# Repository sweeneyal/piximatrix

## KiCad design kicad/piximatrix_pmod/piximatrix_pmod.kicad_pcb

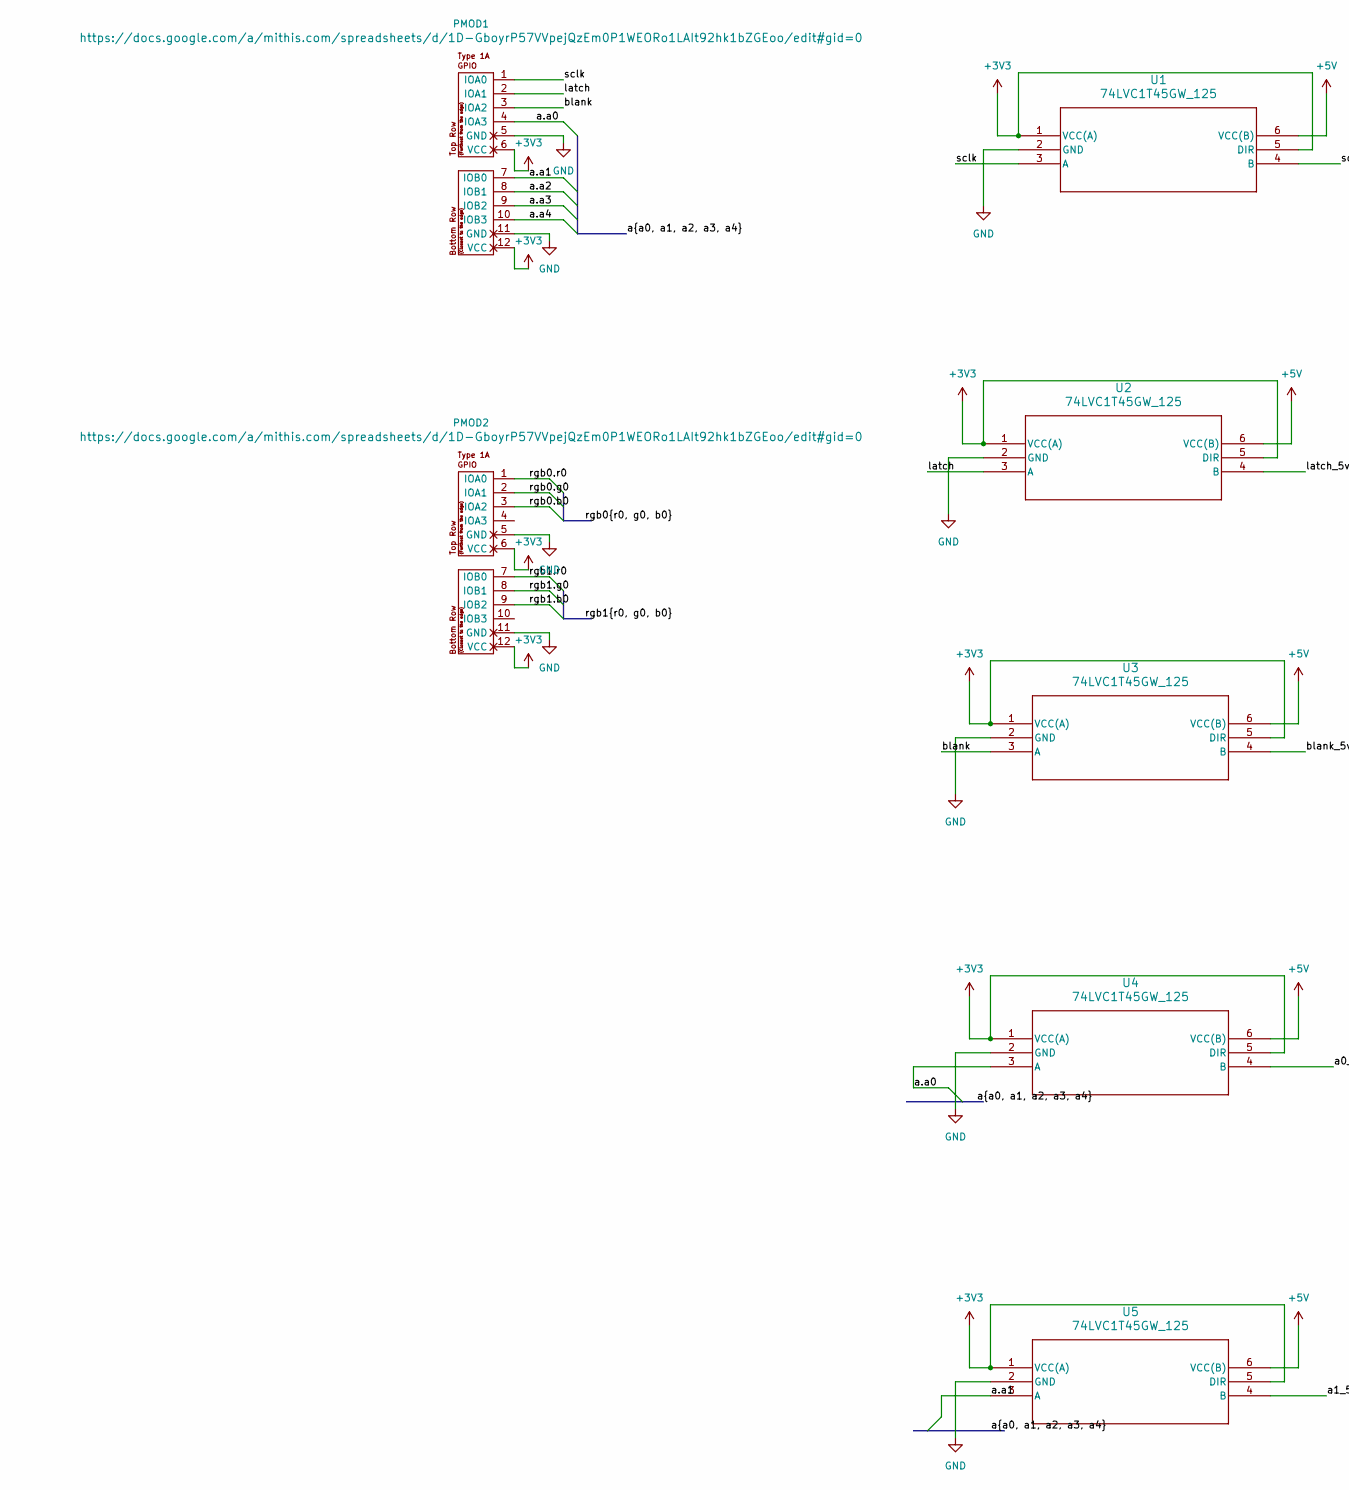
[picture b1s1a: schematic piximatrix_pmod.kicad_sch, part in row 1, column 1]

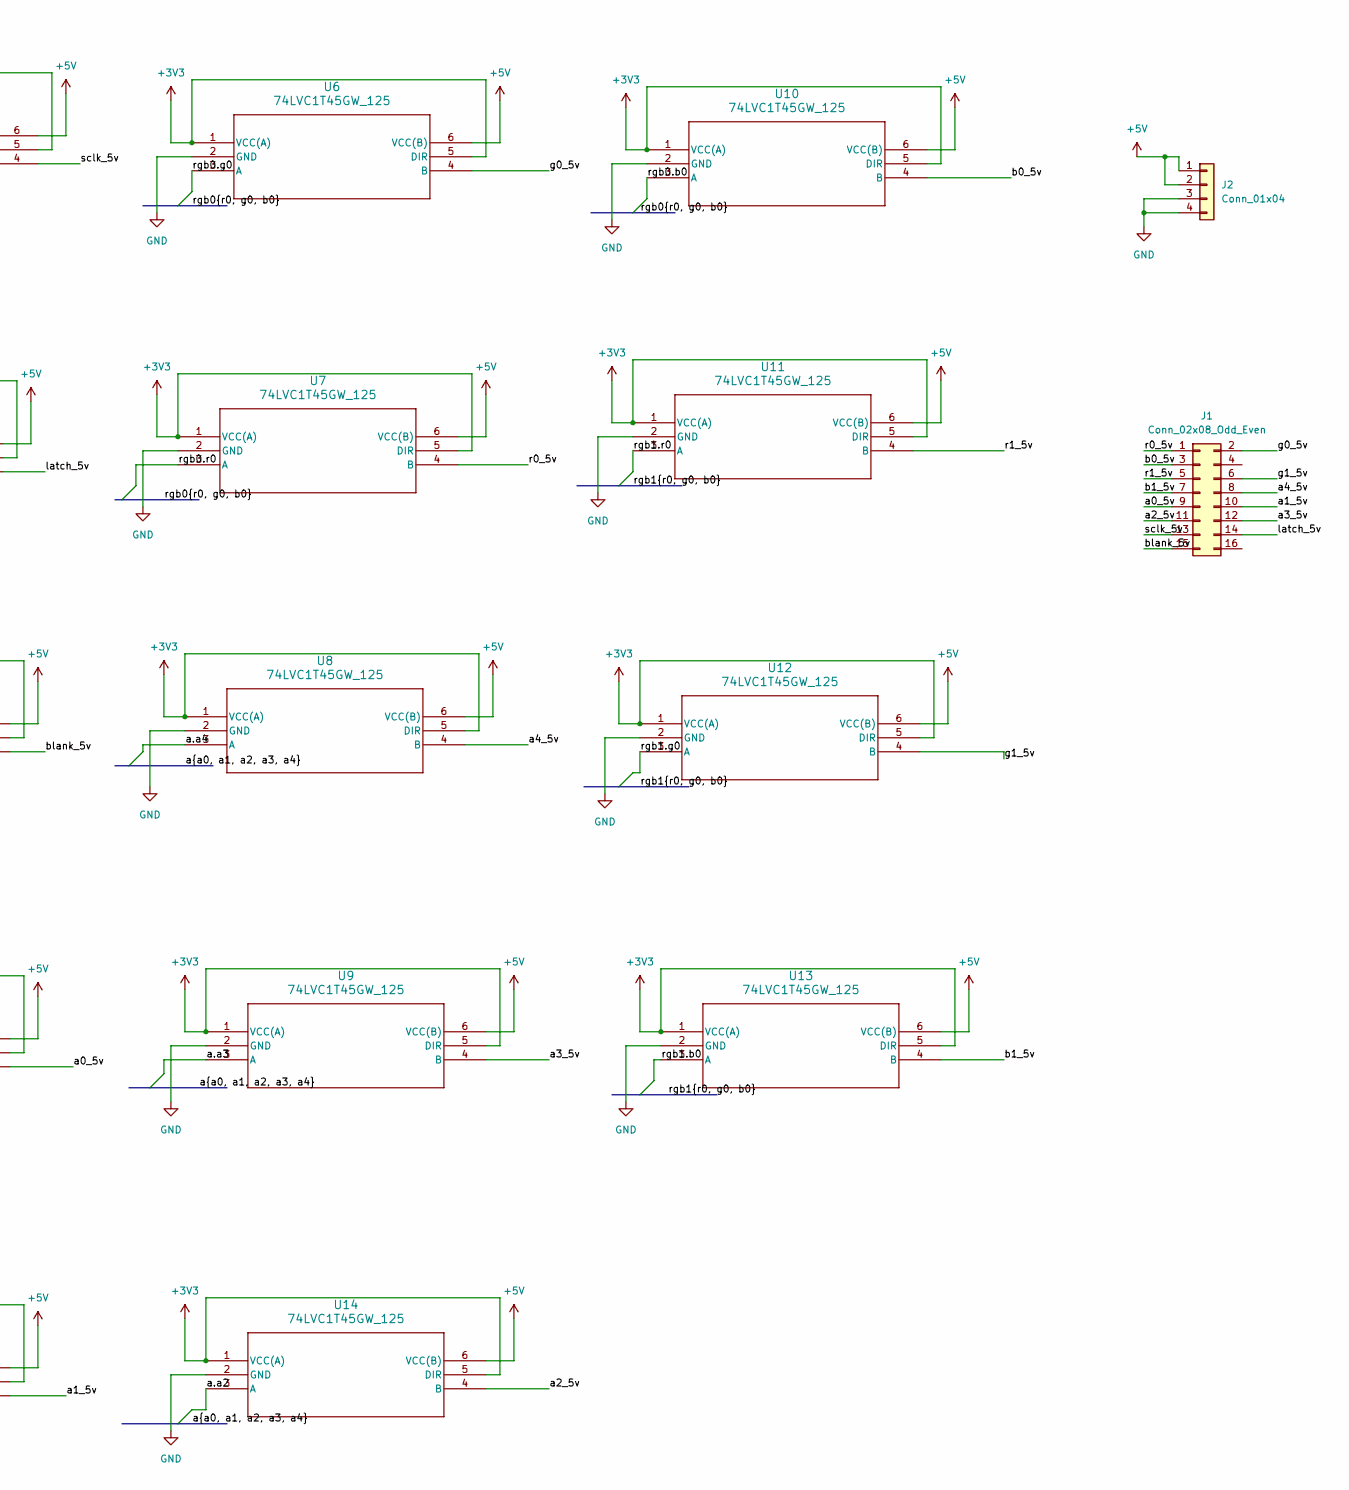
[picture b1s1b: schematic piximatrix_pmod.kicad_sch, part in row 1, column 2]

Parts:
J1: Conn_02x08_Odd_Even; IDC-Header_2x08_P2.54mm_Vertical
J2: Conn_01x04; Molex_KK-396_A-41791-0004_1x04_P3.96mm_Vertical
PMOD1, PMOD2: PMOD-Device-x2-Type-1A-GPIO; pmod_pin_array_6x2
U1, U2, U3, U4, U5, U6, U7, U8, U9, U10, U11, U12, U13, U14: 74LVC1T45GW_125; TSSOP6_SOT363-2_NEX

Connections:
+3V3: PMOD1.6 (VCC), PMOD1.12 (VCC), PMOD2.6 (VCC), PMOD2.12 (VCC), U1.1 (VCC(A)), U1.5 (DIR), U2.1 (VCC(A)), U2.5 (DIR), U3.1 (VCC(A)), U3.5 (DIR), U4.1 (VCC(A)), U4.5 (DIR), U5.1 (VCC(A)), U5.5 (DIR), U6.1 (VCC(A)), U6.5 (DIR), U7.1 (VCC(A)), U7.5 (DIR), U8.1 (VCC(A)), U8.5 (DIR), U9.1 (VCC(A)), U9.5 (DIR), U10.1 (VCC(A)), U10.5 (DIR), U11.1 (VCC(A)), U11.5 (DIR), U12.1 (VCC(A)), U12.5 (DIR), U13.1 (VCC(A)), U13.5 (DIR), U14.1 (VCC(A)), U14.5 (DIR)
+5V: J2.1, J2.2, U1.6 (VCC(B)), U2.6 (VCC(B)), U3.6 (VCC(B)), U4.6 (VCC(B)), U5.6 (VCC(B)), U6.6 (VCC(B)), U7.6 (VCC(B)), U8.6 (VCC(B)), U9.6 (VCC(B)), U10.6 (VCC(B)), U11.6 (VCC(B)), U12.6 (VCC(B)), U13.6 (VCC(B)), U14.6 (VCC(B))
/a0_5v: J1.9, U4.4 (B)
/a1_5v: J1.10, U5.4 (B)
/a2_5v: J1.11, U14.4 (B)
/a3_5v: J1.12, U9.4 (B)
/a4_5v: J1.8, U8.4 (B)
/a.a0: PMOD1.4 (IOA3), U4.3 (A)
/a.a1: PMOD1.7 (IOB0), U5.3 (A)
/a.a2: PMOD1.8 (IOB1), U14.3 (A)
/a.a3: PMOD1.9 (IOB2), U9.3 (A)
/a.a4: PMOD1.10 (IOB3), U8.3 (A)
/b0_5v: J1.3, U10.4 (B)
/b1_5v: J1.7, U13.4 (B)
/blank: PMOD1.3 (IOA2), U3.3 (A)
/blank_5v: J1.15, U3.4 (B)
/g0_5v: J1.2, U6.4 (B)
/g1_5v: J1.6, U12.4 (B)
/latch: PMOD1.2 (IOA1), U2.3 (A)
/latch_5v: J1.14, U2.4 (B)
/r0_5v: J1.1, U7.4 (B)
/r1_5v: J1.5, U11.4 (B)
/rgb0.b0: PMOD2.3 (IOA2), U10.3 (A)
/rgb0.g0: PMOD2.2 (IOA1), U6.3 (A)
/rgb0.r0: PMOD2.1 (IOA0), U7.3 (A)
/rgb1.b0: PMOD2.9 (IOB2), U13.3 (A)
/rgb1.g0: PMOD2.8 (IOB1), U12.3 (A)
/rgb1.r0: PMOD2.7 (IOB0), U11.3 (A)
/sclk: PMOD1.1 (IOA0), U1.3 (A)
/sclk_5v: J1.13, U1.4 (B)
GND: J2.3, J2.4, PMOD1.5 (GND), PMOD1.11 (GND), PMOD2.5 (GND), PMOD2.11 (GND), U1.2 (GND), U2.2 (GND), U3.2 (GND), U4.2 (GND), U5.2 (GND), U6.2 (GND), U7.2 (GND), U8.2 (GND), U9.2 (GND), U10.2 (GND), U11.2 (GND), U12.2 (GND), U13.2 (GND), U14.2 (GND)

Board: 2 copper layers, 18 parts (0 on the bottom side), 31 nets, no tracks yet.

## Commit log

2024-08-04 Rewriting history
2024-08-11 Got the models working, tests are passing. Added additional scripts for analyzing test results
2024-08-11 Getting github workflows working again
2024-08-18 Added a dimmer ability to enable the blank a number of clock cycles early
2025-05-20 Current progress on PMOD schematic in Kicad
